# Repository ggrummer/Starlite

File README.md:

# Starlite
6 and 8-point stars using an FPGA to produce numerous patterns via a simple instruction set.
One doesn't need to know anything about FPGAs to create your own custom displays.
Refer to the "Documents" directory for project documents.
The Eagle directory has the schematic and the board design files.
The Mechanical directory has the 2D CAD files for laser cutting acrylic into star shapes, the 3D CAD files for the optional back covers and 3D CAD files for optional side covers.
The SolUP12 directory has all the FPGA files for the no longer recommended Lattice iCEcube2 build enviorment.
The SolRadi directory has all the FPGA files for the recommended Lattice Radiant build enviorment.

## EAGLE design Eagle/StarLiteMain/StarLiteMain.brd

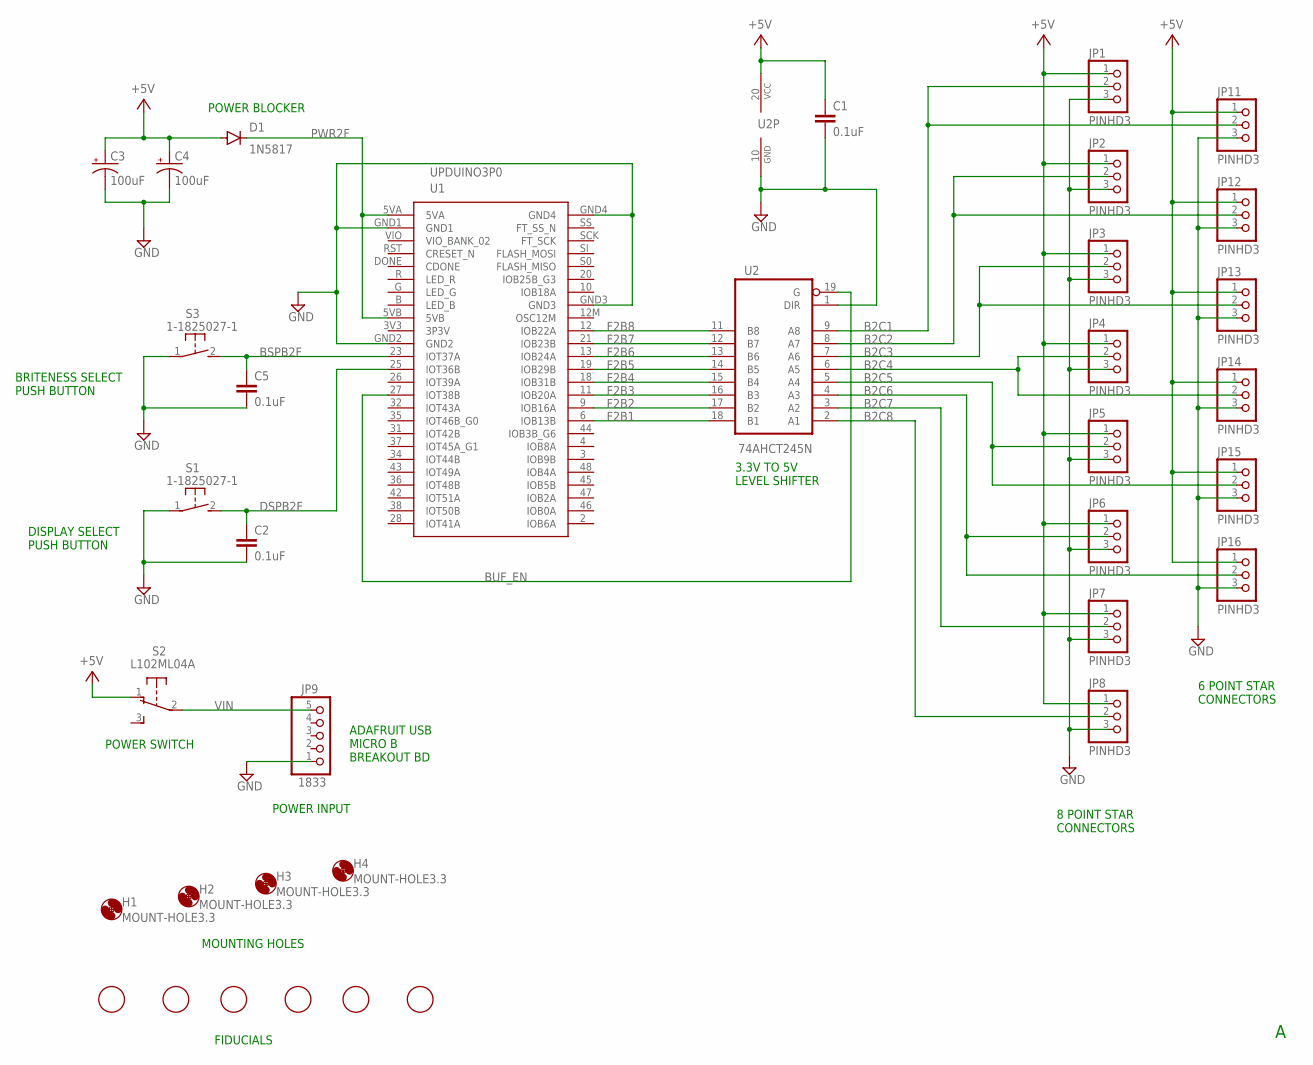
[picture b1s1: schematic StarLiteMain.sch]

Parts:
C1, C2, C5: 0.1uF; C2.5-3
C3, C4: 100uF; E2,5-6
D1: 1N5817; DO41-10
H1, H2, H3, H4: MOUNT-HOLE3.3; 3,3
JP1, JP2, JP3, JP4, JP5, JP6, JP7, JP8, JP11, JP12, JP13, JP14, JP15, JP16: PINHD3; 1X03_50MIL
JP9: 1833; 1X05
S1, S3: 1-1825027-1; B3F-31XX
S2: L102ML04A; SPDT187
U1: UPDUINO3P0
U2: 74AHCT245N; DIL20
U$1, U$2, U$3, U$4, U$5, U$6: FIDUCIAL; FIDUCIAL_1MM

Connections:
+5V: C1.1, C3.+, C4.+, D1.A, JP1.1, JP2.1, JP3.1, JP4.1, JP5.1, JP6.1, JP7.1, JP8.1, JP11.1, JP12.1, JP13.1, JP14.1, JP15.1, JP16.1, S2.1 (O), U2.20 (VCC)
B2C1: JP1.2, JP11.2, U2.9 (A8)
B2C2: JP2.2, JP12.2, U2.8 (A7)
B2C3: JP3.2, JP13.2, U2.7 (A6)
B2C4: JP4.2, JP14.2, U2.6 (A5)
B2C5: JP5.2, JP15.2, U2.5 (A4)
B2C6: JP6.2, JP16.2, U2.4 (A3)
B2C7: JP7.2, U2.3 (A2)
B2C8: JP8.2, U2.2 (A1)
BSPB2F: C5.1, S3.2 (S), U1.23 (IOT37A)
BUF_EN: U1.27 (IOT38B), U2.19 (G)
DSPB2F: C2.1, S1.2 (S), U1.25 (IOT36B)
F2B1: U1.6 (IOB13B), U2.18 (B1)
F2B2: U1.9 (IOB16A), U2.17 (B2)
F2B3: U1.11 (IOB20A), U2.16 (B3)
F2B4: U1.18 (IOB31B), U2.15 (B4)
F2B5: U1.19 (IOB29B), U2.14 (B5)
F2B6: U1.13 (IOB24A), U2.13 (B6)
F2B7: U1.21 (IOB23B), U2.12 (B7)
F2B8: U1.12 (IOB22A), U2.11 (B8)
GND: C1.2, C2.2, C3.-, C4.-, C5.2, JP1.3, JP2.3, JP3.3, JP4.3, JP5.3, JP6.3, JP7.3, JP8.3, JP9.1, JP11.3, JP12.3, JP13.3, JP14.3, JP15.3, JP16.3, S1.1, S3.1, U1.GND1, U1.GND2, U1.GND3, U1.GND4, U2.1 (DIR), U2.10 (GND)
PWR2F: D1.C, U1.5VA, U1.5VB
VIN: JP9.5, S2.2

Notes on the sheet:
POWER INPUT
POWER SWITCH
POWER BLOCKER
3.3V TO 5V LEVEL SHIFTER
DISPLAY SELECT PUSH BUTTON
ADAFRUIT USB MICRO B BREAKOUT BD
8 POINT STAR CONNECTORS
6 POINT STAR CONNECTORS
MOUNTING HOLES
FIDUCIALS
BRITENESS SELECT PUSH BUTTON

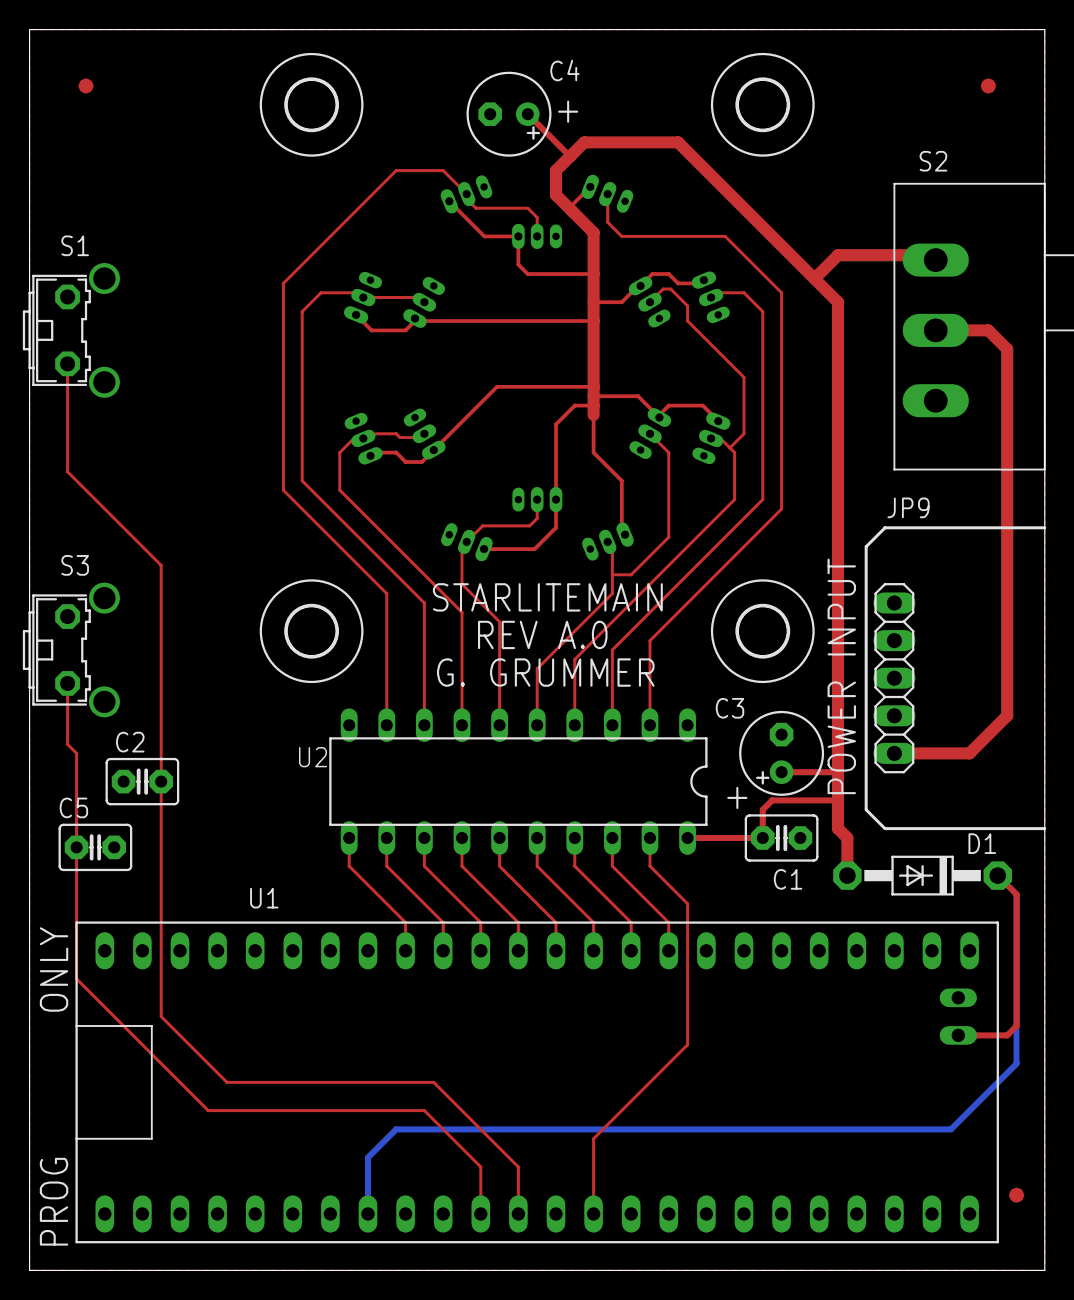
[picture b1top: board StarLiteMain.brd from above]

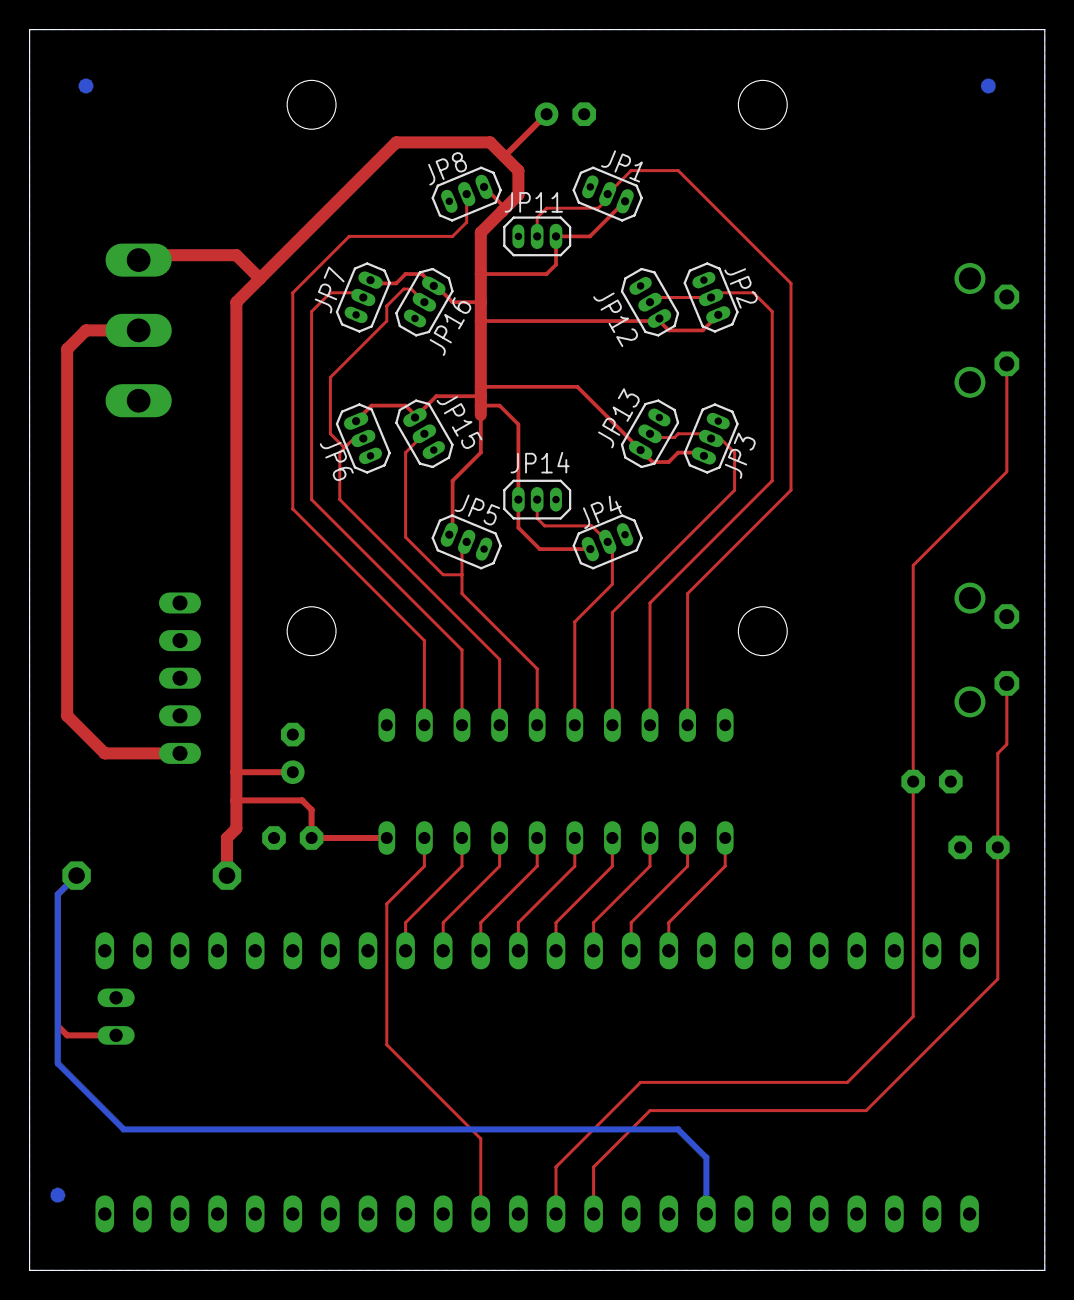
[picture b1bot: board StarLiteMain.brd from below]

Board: 2 copper layers, 68.6 x 83.8 mm, 36 parts (17 on the bottom side), 23 nets.

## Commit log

2020-08-12 Deleted patterns>Archive directory
2020-08-12 Added documents and PCB project
    Added documentation and the Eagle PCB project files.
2020-08-12 Acrylic Stars
    Added DXF file for laser cutting the acrylic stars
2020-08-12 Create starliteBOM.xlsx
    Added the project parts list
2020-08-14 Update LED_StarLiteUP_Instruction.xlsx
    Eliminated footnote 2. It no longer applies.
2020-08-25 Added documentation
    Added initial versions of user's manual and installation guide. Updated block diagram. Added notes to the parts list.
2020-08-25 Added Output Files
    Added files needed for quick custom displays.
2020-09-08 Updated User's Manual
    Updated User's Manual and deleted redundent documents. The parts list was moved to documents and the Parts directory was deleted.
2020-09-11 Additions and cleanup
    Added assembly instructions. Added instruction descriptions to user's manual. Cleaned up spreadsheet.
2020-09-11 Update README.md
    Fix typo
2020-09-13 Added Back Cover CAD Files
    Added back cover 3D printer CAD Files. Both the STL files and the OnShape CAD file links are included.
2020-09-13 Update README.md
    Added notes about the board and mechanical directories.
2020-09-13 Replaced Word docs with PDFs
    Added PDF documents and deleted Word versions of those documents.
2020-09-14 Update Starlite Assembly Instructions.pdf
    Clarified which pins on the UPduino board must be soldered to the StarLiteMain board.
2020-09-14 Update Starlite User's Manual.pdf
    Changed link to video with a better thumbnail.
2020-09-24 Added Gerber Files
2020-09-29 Update Starlite User's Manual.pdf
    Replace links to video.
2020-10-03 Update Starlite Assembly Instructions.pdf
    Fixed typos.
2020-10-07 Update Starlite User's Manual.pdf
    Replaced Google Drive with Vimeo video link.
2020-10-20 Minor update. Parts list deleted.
    Use parts list in Documents directory.
2020-10-20 Moved 5V & GND Holes
    Moved 5V & GND hole pair
2020-10-20 Moved 5V & GND Hole Pair
2020-11-01 Added Halloween spiral pattern
2020-12-13 Update starlitePL.xlsx
    Fixed typo
2021-01-13 Updated burst8 pattern
    Made burst8 delays equal to burst6 delays.
2021-03-10 Reorganized/Added FPGA files
    Moved iCEcube2 FPGA files into SolUP12 directory.
    Added Radiant FPGA files to SolRadi directory.
2021-03-10 Moved testbench files
2021-03-11 Moved iCEcube2 constrains directory
2021-03-11 Made document iCEcube2 specific
2021-04-24 Added Radiant User's Manual
    Renamed iCEcube2 User's Manual.
    Added Radiant User's Manual.
2021-04-29 Expanded Chase module features
2021-05-11 Sides for 8 point star
    Added 3D printed side files for the 8 point star.
2021-05-24 Update sub_framer.vhd
    Made the comments and code a bit more clear.
2021-05-24 Side Cover Additions
    Added 6 point star sides. Modified 6 & 8 point back covers to work with star sides.
2021-05-24 Update README.md
    Added 3D printed side covers.
2021-05-28 Update starlitePL.xlsx
    Listed alternatives for obsolete LED string.
2021-05-28 Update StarCoverMain8c.stl
    Made a little bit more space between the sections that the legs mount to. Needed to fit the sides better.
2021-05-30 Update Right6All.stl
    Increased diameter of locking feature between right and left side prints by 0.005".
2021-06-04 Update starlitePL.xlsx
    Added more details on replacement LED strips.
2021-12-13 Reversed individual point blocking order
    Reversed individual point blocking order so point 0 was the first physical point.
2022-04-17 Sides for 1/8" Inner Acrylic
    Added files for Starlite sides using 1/8" thick inner acrylic.
2022-06-09 Excluded Color Repeats
    When using random colors (in instruction 3) one can now choose whether to allow them to repeat or to exclude repeats.
2022-06-09 Added additional files
2022-06-15 Brought file up to date with RTL
2025-02-05 STL files for 1/16" thick inner acrylic
    STL files for 1/16" thick inner acrylic
